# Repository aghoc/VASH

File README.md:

<p align="center">
  <strong>VASH</strong> &nbsp; <em>Vision-Anchored Self-Healing Prosthetic Hand</em><br>
  근전도와 비전 AI를 결합한 사용자 중심 로봇 의수
</p>

<p align="center">
  <a href="#overview">Overview</a> ·
  <a href="#배경과-목표">프로젝트 소개</a> ·
  <a href="#시스템-구성">시스템 구성</a> ·
  <a href="#제작-및-시연">제작 및 시연</a> ·
  <a href="#평가-결과">평가 결과</a> ·
  <a href="#향후-과제">향후 과제</a>
</p>

---

## Overview

다채널 근전도(EMG)와 영상 기반 인공지능을 결합해 사용자의 손동작 의도와 주변 물체를 함께 고려하는 로봇 의수 연구 프로젝트입니다. 근육 피로와 신호 특성 변화에 대응하는 자가치유 제어와 객체 인식 기반 파지 보조를 통해, 일상 환경에 적응하는 사용자 중심의 의수 제어를 목표로 합니다.

> **프로젝트 상태:** 연구 및 개발 단계입니다. Jetson 비전 모듈은 [src/vision/](src/vision/), EMG 판단·의수 제어와 실행 앱은 [src/emg_hand_control/](src/emg_hand_control/), 보드·펌웨어·전극 밴드는 [hardware/](hardware/)에 있습니다. 비전과 EMG 의 실시간 통합은 진행 중입니다. 아래 평가는 각 연구 조건에 한정됩니다.

## 배경과 목표

근전도 기반 의수는 근육에서 발생하는 전기 신호를 이용해 사용자의 동작 의도를 추정합니다. 하지만 근육 피로, 전극 위치, 팔 자세가 바뀌면 신호 특성도 달라져 동작 분류와 제어가 불안정해질 수 있습니다. 또한 EMG만으로는 사용자가 잡으려는 물체의 형태와 크기를 알기 어렵습니다.

VASH는 이 두 문제를 함께 다룹니다.

- **사용자 의도 인식:** 다채널 EMG로 손동작을 분류합니다.
- **신호 변화 대응:** 자가치유(Self-Healing) 제어를 통해 피로와 신호 특성 변화에 따른 성능 저하를 보완하고자 합니다.
- **환경 인식과 파지 보조:** 카메라 영상에서 파지 대상을 찾고 물체에 적합한 그립과 손가락 개구량을 결정하도록 설계합니다.

## 시스템 구성

| 구성 요소 | 역할 |
| --- | --- |
| 16채널 EMG 센서 | 팔의 다채널 근전도 신호 측정 |
| ADS1299 신호 획득 모듈 | EMG 신호 획득 |
| ESP32-S3 | 센서 데이터 처리 및 시스템 제어 |
| 전방 카메라 | 사용자의 시야에 있는 물체 영상 획득 |
| Jetson Orin Nano | EMG·영상 기반 인식과 제어 처리 |
| ORCA Hand | 16자유도 로봇 손을 이용한 파지 동작 |

시스템은 EMG를 통해 **사용자가 어떤 동작을 원하는지** 추정하고, 영상에서 **어떤 물체를 잡으려는지**에 관한 정보를 얻습니다. 두 정보를 바탕으로 로봇 손의 동작을 보조하는 것이 목표입니다.

### EMG 기반 의도 인식과 자가치유

초기에는 팔에 전극을 직접 부착해 근전도 신호를 측정했습니다. 이후 센서 밴드를 직접 설계·제작해 착용하고 손동작 데이터를 수집했습니다.

| 초기 전극 부착 및 근전도 측정 | 직접 설계한 센서 밴드를 이용한 데이터 수집 |
| --- | --- |
|  |  |

EMG 센서에서 얻은 신호로 휴식, 주먹, 세손가락, 집기와 같은 손동작을 구분합니다. 장시간 사용 중 근육 피로가 쌓이거나 측정 조건이 달라지면 같은 동작의 신호도 변할 수 있습니다. VASH의 자가치유 제어는 이러한 신호 변화에 적응해 동작 인식 성능의 저하를 보완하는 것을 목표로 합니다.

| 휴식 | 주먹 |
| --- | --- |
|  |  |
| 세손가락 | 집기 |
|  |  |

*동작별 다채널 EMG 신호 예시. 그림에는 각 동작에 대한 측정 신호가 표시되어 있습니다.*

### Vision AI 기반 파지 보조

전방 카메라 영상에서 객체를 인식하고, 화면 중심과의 거리를 고려하는 **Center Bias** 방식으로 파지 대상을 선정합니다. 선택한 물체의 크기와 형태에 관한 정보를 이용해 적합한 그립과 목표 손가락 개구량을 산출하도록 설계했습니다.

*전방 영상에서 물체를 인식하고 파지 대상을 선정하는 모습.*

*객체 인식 및 대상 선정 화면 예시.*

### 공개된 Jetson 비전 코드

현재 기본 모델은 추가학습하지 않은 공식 **YOLO26m**이며 Jetson에서 생성한 TensorRT FP16 엔진을 사용합니다. ELP IMX291 영상에서 배경 37종을 제외한 물체 43종을 표시하고, 그립을 지원하는 8종에서 중앙 타깃을 선택합니다. 캔·펜 보조 모델은 기본 실행에서 제외했습니다.

- [비전 모듈 설명과 테스트](src/vision/README.md)
- [Jetson 설치·엔진 생성·실행](src/vision/deployment/JETSON_RUNBOOK.md)
- [Jetson → ESP32 UART 규격](src/vision/docs/UART_PROTOCOL.md)

브라우저 뷰어는 그립 제안을 표시하며 UART 송신은 별도 CLI 실행 기능입니다. 가중치·엔진·데이터는 Git에 포함하지 않으며, 모델 복원 스크립트를 제공합니다. 실제 카메라 정확도와 개구량 실측 보정은 추가 검증이 필요합니다.

### 로봇 손과 파지 시뮬레이션

16자유도 ORCA Hand를 사용해 다양한 손가락 동작과 파지를 구현합니다. 시뮬레이션에서는 캔, 펜, 스마트폰, 동전 등 형태가 다른 물체를 대상으로 접근부터 잡기, 들기, 유지까지의 과정을 살펴보았습니다.

*물체와 그립 유형에 따른 파지 동작 시퀀스.*

## 제작 및 시연

| EMG 센서 밴드 착용 시연 | ORCA Hand 구동 테스트 |
| --- | --- |
|  |  |

| 로봇 손 조립 | 손가락 부품 조립 |
| --- | --- |
|  |  |

| 손 부품 3D 프린팅 | 손 부품 3D 프린팅 |
| --- | --- |
|  |  |

## 평가 결과

연구에서는 근육 피로에 따른 동작 분류와 EMG·비전 융합에 따른 파지 선택을 평가했습니다. 아래 그림은 해당 실험 및 분석의 결과를 보여줍니다.

### 피로 상태별 동작 분류

휴식 상태와 피로 측정 시점에 따른 네 가지 동작의 분류 정확도를 비교했습니다. 동작과 측정 시점에 따라 정확도가 달라지는 양상을 확인할 수 있습니다.

### EMG·비전 융합 평가

실측 EMG 기반 오프라인 평가에서 EMG만 사용한 경우와 EMG·비전을 융합한 경우의 파지 선택 오류를 비교했습니다. 그림은 평가한 조건에서 융합 방식의 오류가 더 낮은 결과와, 비전 인식률에 따른 오류 변화를 보여줍니다.

이 결과는 해당 평가 조건에 한정됩니다. 참가자 수, 데이터 수집 및 분할 방법, 자가치유 모델의 구체적인 동작과 실사용 환경에서의 성능은 추가 문서와 검증이 필요합니다. 시뮬레이션 결과를 실제 사용자 대상 성능으로 해석해서는 안 됩니다.

## 저장소 구조

```text
VASH/
├── README.md
├── LICENSE
├── fig/                  # 시스템, EMG 신호 및 평가 결과 이미지
├── docs/                 # 실행·녹화 가이드, 분석 결과
├── hardware/             # ADS1299 보드, ESP32-S3 펌웨어, 전극 밴드
└── src/
    ├── emg_hand_control/ # EMG 판단, ORCA Hand 제어, 실행 앱, Jetson 설치
    └── vision/           # Jetson YOLO26m 검출·타깃 안정화·그립 제안 모듈
```

비전 모듈은 [src/vision/README.md](src/vision/README.md), EMG·의수 제어는 [src/emg_hand_control/README.md](src/emg_hand_control/README.md)를 따릅니다.

## 향후 과제

- 자가치유 제어와 EMG·비전 융합 방식의 구현 및 평가 절차 문서화
- 실제 사용 환경에서의 동작 인식, 파지 성능 및 장시간 안정성 검증
- 전극 위치와 팔 자세 변화 등 다양한 사용 조건에서의 평가
- 하드웨어 경량화와 착용성 개선
- 상지 절단자를 위한 의수 및 재활 보조 기술로의 확장 가능성 검토

## 라이선스

- 코드: [MIT](LICENSE)
- `hardware/demo_glove/`: [CC BY-SA 4.0](hardware/demo_glove/LICENSE.md)
- 그 밖의 하드웨어 파일과 이미지는 위 라이선스에 포함되지 않습니다.

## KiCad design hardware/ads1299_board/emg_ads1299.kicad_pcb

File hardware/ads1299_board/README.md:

# ADS1299 EMG Board

8채널 근전도 측정 보드입니다. ESP32-S3-DevKitC-1 위에 소켓으로 얹어 사용합니다.

위 그림은 KiCad PCB 파일에서 만든 렌더링입니다.

## Specifications

| Item | Value |
|---|---|
| Board | 27 × 96 mm, 2 layers, ENIG |
| AFE | TI ADS1299IPAG (TQFP-64), 8 channels, 24-bit |
| Stream settings | 2000 SPS, gain 24 (±187.5 mV), differential + BIAS |
| Input filter (per channel) | 10 kΩ, 4.7 nF differential, 47 pF common mode |
| Analog supply | 5 V from MAX1683 charge pump + LT1763 LDO |
| Digital supply | 3.3 V from ESP32-S3 |
| Host link | ESP32-S3 UART USB, 921600 baud |

## Block diagram

```mermaid
flowchart LR
    E[Electrodes<br/>8 pairs + BIAS] --> J1[J1]
    J1 --> F[RC input filter]
    F --> U1[ADS1299]
    U1 -- BIAS --> J1
    U1 -- SPI, DRDY --> M[ESP32-S3]
    M -- USB UART --> PC[PC]

    V5[USB 5 V] --> U2[MAX1683<br/>charge pump]
    U2 --> RC[RC filter] --> U3[LT1763<br/>5 V LDO]
    U3 -- AVDD --> U1
    M -- 3V3 DVDD --> U1
```

Analog and digital ground are joined at a single point (NT1).

## Main parts

| Ref | Part | Function |
|---|---|---|
| U1 | ADS1299IPAG | 8-channel analog front end |
| U2 | MAX1683EUK+T | Charge pump |
| U3 | LT1763CS8-5#PBF | 5 V low-noise LDO |
| C1–C8 | 4.7 nF C0G | Differential input filter |
| C9–C24 | 47 pF C0G | Common-mode input filter |
| R18, C25 | 1 MΩ, 1.5 nF | BIAS feedback |
| R24 | 10 Ω | Charge pump RC filter |
| C31 | 100 µF | VCAP1 |
| C47, C48 | 1 µF | Additional AVDD decoupling |
| J1 | 2×9 terminal | Electrode wires |
| J4, J5 | 1×22 socket | ESP32-S3-DevKitC-1 |

Full list with part numbers: [`fabrication/BOM_handsolder.csv`](fabrication/BOM_handsolder.csv)

## J1 electrode terminal

Top view, with the silkscreen labels on the board.

| | | | | | | | | | |
|---|---|---|---|---|---|---|---|---|---|
| Upper row | 1N | 2N | 3N | 4N | BI | 5N | 6N | 7N | 8N |
| Lower row | 1P | 2P | 3P | 4P | GN | 5P | 6P | 7P | 8P |

- `nN`, `nP`: channel n inputs
- `BI`: BIAS electrode
- `GN`: analog ground for scope probes, not an electrode

Clean flux off with IPA after soldering. The ADS1299 inputs are high impedance.

## ESP32-S3 connections

| Board | Signal | ESP32-S3 |
|---|---|---|
| J4.1 | DVDD | 3V3 |
| J4.15 | DRDY | GPIO9 |
| J4.16 | CS | GPIO10 |
| J4.17 | DIN | GPIO11 |
| J4.18 | SCLK | GPIO12 |
| J4.19 | DOUT | GPIO13 |
| J4.20 | START | GPIO14 |
| J4.21 | 5V | 5V |
| J5.17 | RESET | GPIO47 |
| J5.18 | PWDN | GPIO21 |
| J4.22, J5.1, J5.21, J5.22 | GND | GND |

GPIO47 runs at 1.8 V on WROOM-2 modules (`V` suffix), which is too low for RESET. Check the module before use. See [`docs/design_review.md`](docs/design_review.md).

## Test results

Measured on an assembled board with the self-test firmware (2026-11-02).

| Test | Result |
|---|---|
| AVDD / DVDD | 5.008 V / 3.093 V |
| Input-shorted noise, 2000 SPS, gain 24 | 0.394 µVrms (worst channel) |
| Internal test signal | 3.70 mVpp, 2.00 Hz (expected 3.75 mVpp) |

KiCad 10 ERC and DRC report no errors (2026-11-04).

## Files

```
emg_ads1299.kicad_pro    KiCad project
emg_ads1299.kicad_sch    Schematic
emg_ads1299.kicad_pcb    PCB
fp-lib-table             Footprint libraries
sym-lib-table            Symbol libraries
lib/
  symbols/               Project symbols
  footprints/            Project footprints
  3d/                    3D models
fabrication/
  gerber/                Gerber and drill files
  BOM_handsolder.csv     BOM with DigiKey part numbers
  BOM_jlcpcb.csv         BOM for JLCPCB assembly
  CPL_jlcpcb.csv         Placement file for JLCPCB assembly
docs/
  schematic.pdf          Schematic
  design_review.md       Design review
  CHANGELOG.md           Board revision notes
  images/                Board renders
```

Open `emg_ads1299.kicad_pro` in KiCad 10 or later. Library paths are relative to the project folder.

To regenerate the renders:

```bash
kicad-cli pcb render --side top --quality high --width 900 --height 2400 --background transparent -o top.png emg_ads1299.kicad_pcb
kicad-cli sch export pdf -o docs/schematic.pdf emg_ads1299.kicad_sch
```

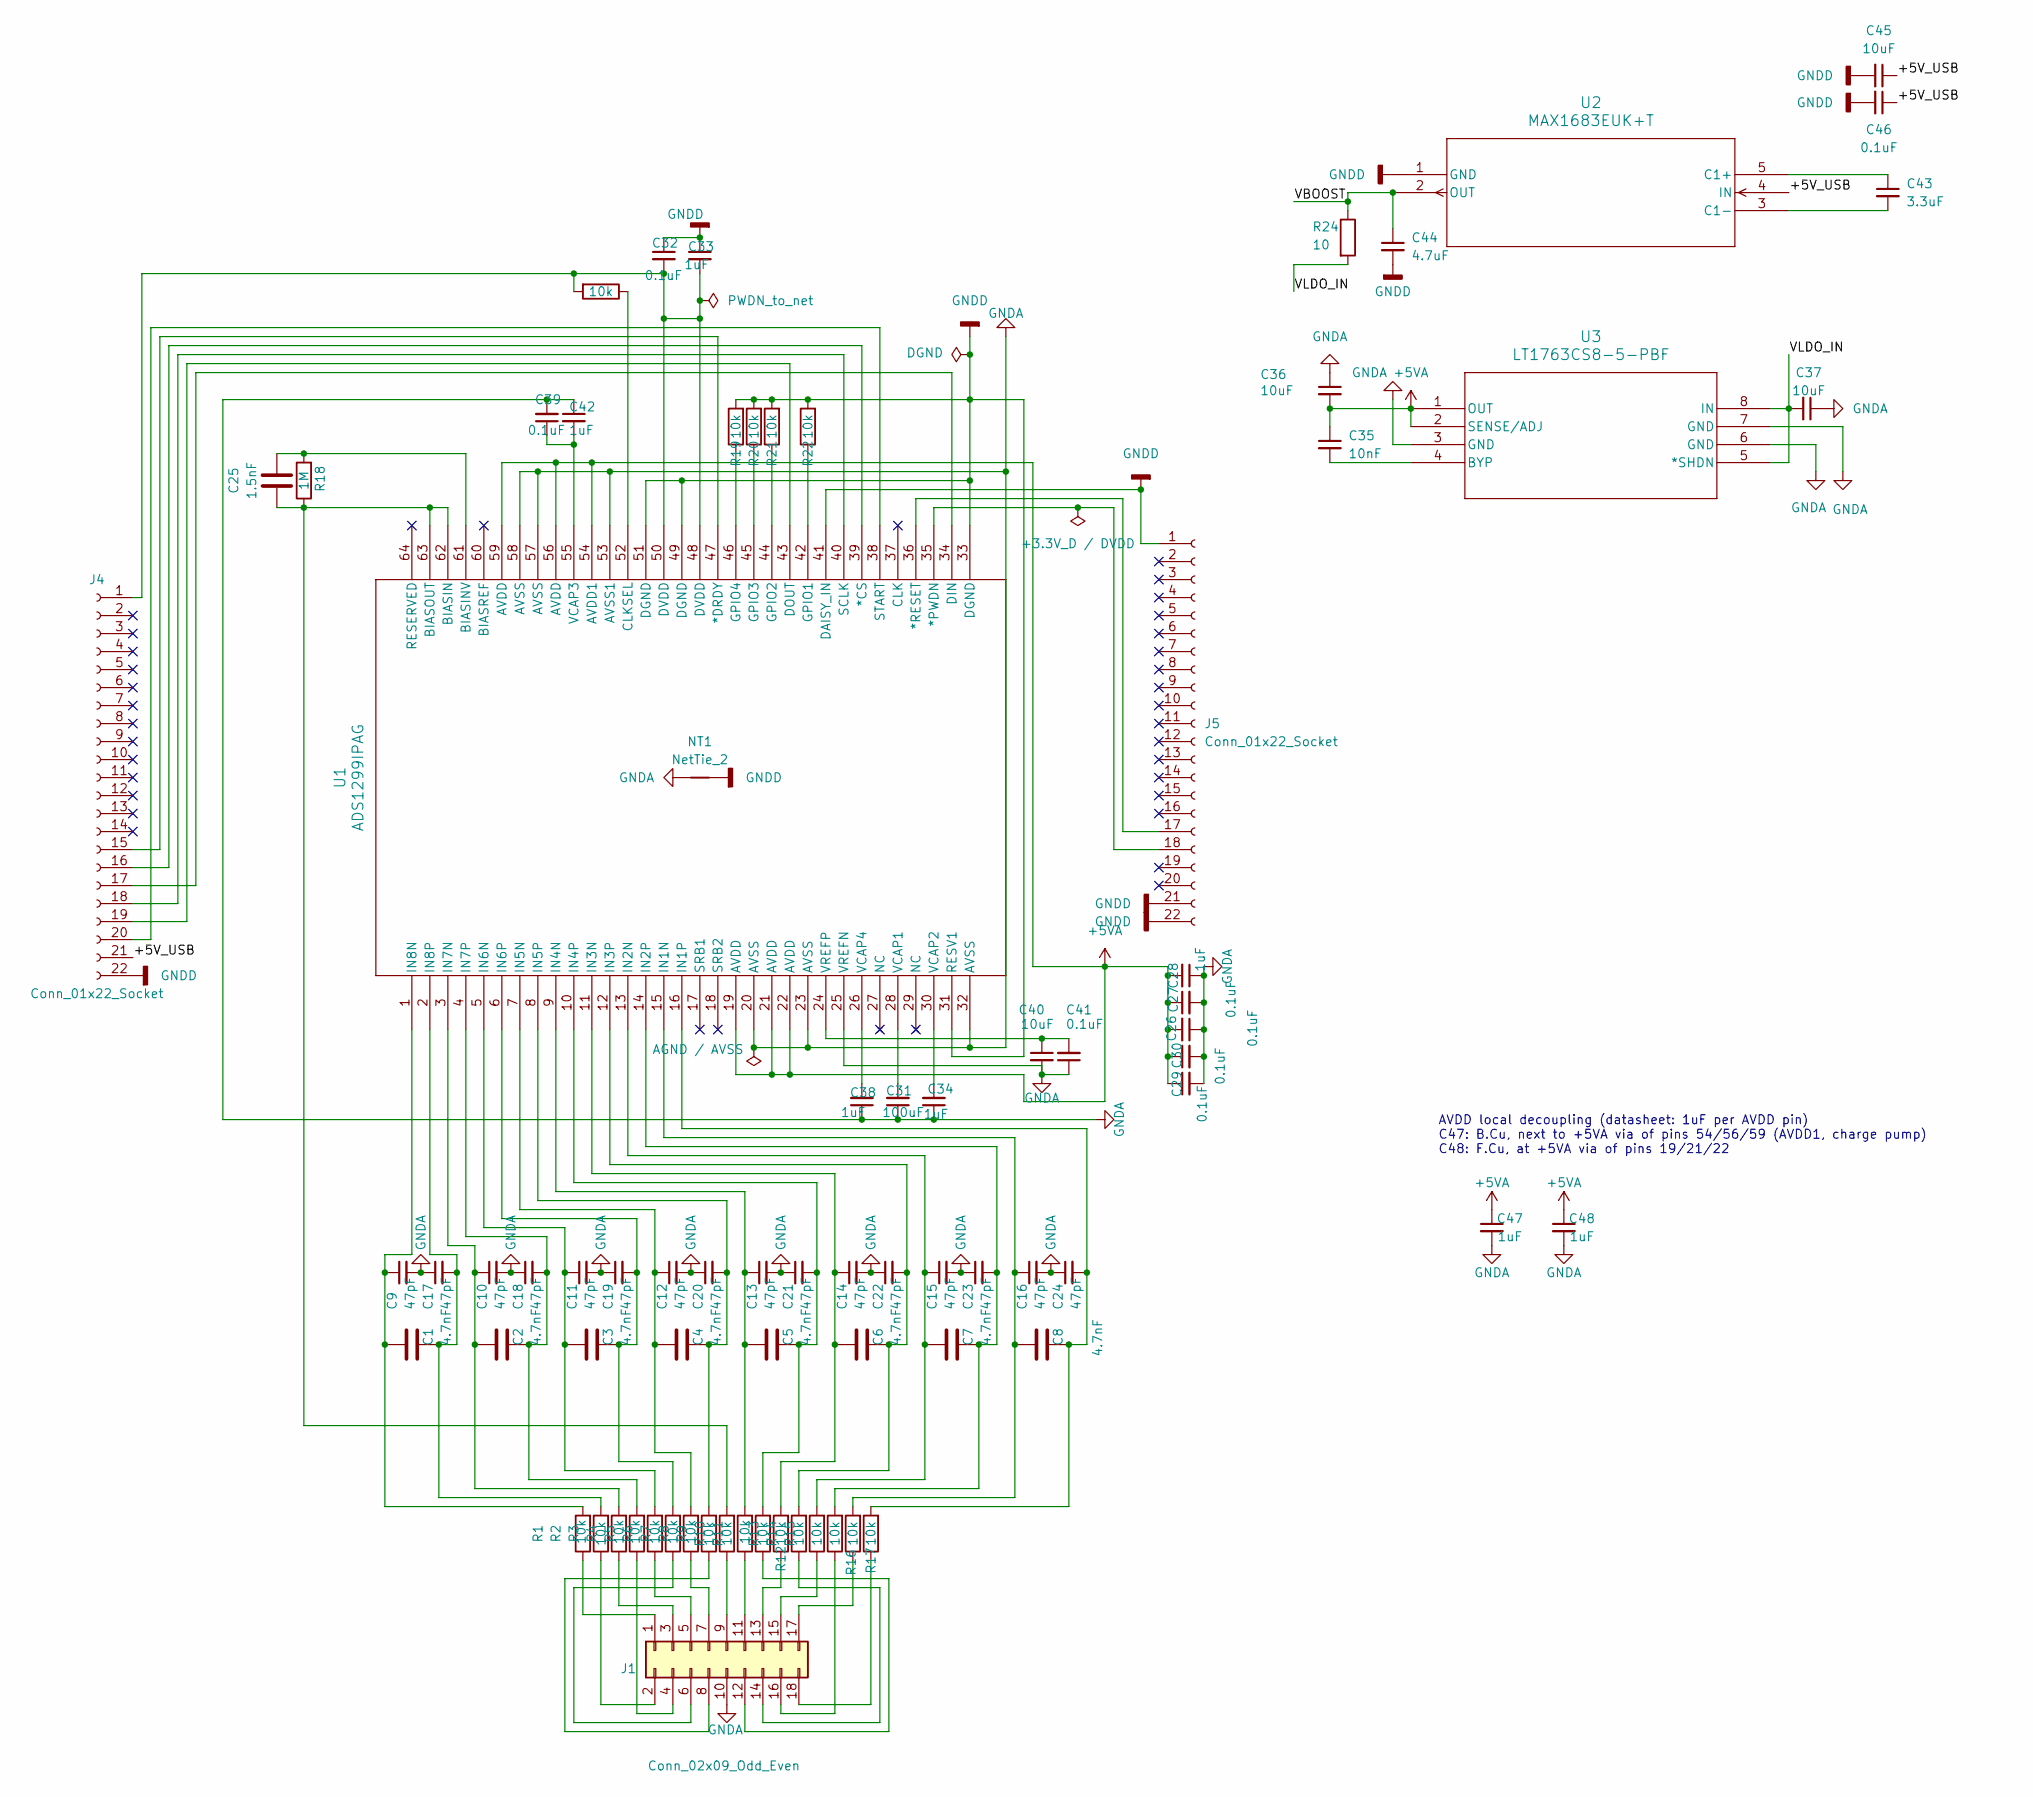
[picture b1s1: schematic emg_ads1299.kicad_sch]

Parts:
C1, C2, C3, C4, C5, C6, C7, C8: 4.7nF; C_1206_3216Metric_Pad1.33x1.80mm_HandSolder
C9, C10, C11, C12, C13, C14, C15, C16, C17, C18, C19, C20, C21, C22, C23, C24: 47pF; C_0805_2012Metric_Pad1.18x1.45mm_HandSolder
C25: 1.5nF; C_0805_2012Metric_Pad1.18x1.45mm_HandSolder
C26, C27, C29, C30, C32, C39, C41, C46: 0.1uF; C_0805_2012Metric_Pad1.18x1.45mm_HandSolder
C28, C33, C34, C38, C42, C47, C48: 1uF; C_0805_2012Metric_Pad1.18x1.45mm_HandSolder
C31: 100uF; C_0805_2012Metric_Pad1.18x1.45mm_HandSolder
C35: 10nF; C_1206_3216Metric_Pad1.33x1.80mm_HandSolder
C36, C37: 10uF; C_1206_3216Metric_Pad1.33x1.80mm_HandSolder
C40, C45: 10uF; C_0805_2012Metric_Pad1.18x1.45mm_HandSolder
C43: 3.3uF; C_0805_2012Metric_Pad1.18x1.45mm_HandSolder
C44: 4.7uF; C_0805_2012Metric_Pad1.18x1.45mm_HandSolder
J1: Conn_02x09_Odd_Even; WireTerminal_2x09_P2.54mm
J4, J5: Conn_01x22_Socket; PinSocket_1x22_P2.54mm_Vertical
NT1: NetTie_2; NetTie-2_SMD_Pad0.5mm
R1, R2, R3, R4, R5, R6, R7, R8, R9, R10, R11, R12, R13, R14, R15, R16, R17, R19, R20, R21, R22, R23: 10k; R_0603_1608Metric_Pad0.98x0.95mm_HandSolder
R18: 1M; R_0603_1608Metric_Pad0.98x0.95mm_HandSolder
R24: 10; R_0805_2012Metric_Pad1.20x1.40mm_HandSolder
U1: ADS1299IPAG; PAG64_TEX
U2: MAX1683EUK+T; SOT-23-5
U3: LT1763CS8-5-PBF; SO-8_S_LIT

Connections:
+5VA: C26.2, C27.1, C28.2, C29.1, C30.1, C35.1, C36.2, C47.1, C48.1, U1.19 (AVDD), U1.21 (AVDD), U1.22 (AVDD), U1.54 (AVDD1), U1.56 (AVDD), U1.59 (AVDD), U3.1 (OUT), U3.2 (SENSE/ADJ)
/+5V_USB: C45.1, C46.1, J4.21, U2.4 (IN)
/VBOOST: C44.1, R24.1, U2.2 (OUT)
/VLDO_IN: C37.2, R24.2, U3.5 (*SHDN), U3.8 (IN)
GNDA: C9.2, C10.2, C11.2, C12.2, C13.2, C14.2, C15.2, C16.2, C17.1, C18.1, C19.1, C20.1, C21.1, C22.1, C23.1, C24.1, C26.1, C27.2, C28.1, C29.2, C30.2, C31.1, C34.1, C36.1, C37.1, C38.1, C39.2, C40.2, C41.1, C42.1, C47.2, C48.2, J1.10, NT1.1, U1.20 (AVSS), U1.23 (AVSS), U1.25 (VREFN), U1.32 (AVSS), U1.53 (AVSS1), U1.57 (AVSS), U1.58 (AVSS), U3.3 (GND), U3.6 (GND), U3.7 (GND)
GNDD: C32.1, C33.1, C44.2, C45.2, C46.2, J4.22, J5.1, J5.21, J5.22, NT1.2, R19.2, R20.2, R21.2, R22.2, U1.31 (RESV1), U1.33 (DGND), U1.41 (DAISY_IN), U1.49 (DGND), U1.51 (DGND), U2.1 (GND)
unnamed: J1.1, R1.1
unnamed: J1.2, R2.1
unnamed: J1.3, R3.1
unnamed: J1.4, R4.1
unnamed: J1.5, R5.1
unnamed: J1.6, R6.1
unnamed: J1.7, R7.1
unnamed: J1.8, R8.1
unnamed: J1.9, R9.1
unnamed: J1.11, R10.1
unnamed: J1.12, R11.1
unnamed: J1.13, R12.1
unnamed: J1.14, R13.1
unnamed: J1.15, R14.1
unnamed: J1.16, R15.1
unnamed: J1.17, R16.1
unnamed: J1.18, R17.1
unnamed: C32.2, C33.2, J4.1, R23.2, U1.48 (DVDD), U1.50 (DVDD)
unnamed: J4.15, U1.47 (*DRDY)
unnamed: J4.16, U1.39 (*CS)
unnamed: J4.17, U1.34 (DIN)
unnamed: J4.18, U1.40 (SCLK)
unnamed: J4.19, U1.43 (DOUT)
unnamed: J4.20, U1.38 (START)
unnamed: J5.17, U1.36 (*RESET)
unnamed: J5.18, U1.35 (*PWDN)
unnamed: C25.1, R9.2, R18.1, U1.62 (BIASIN), U1.63 (BIASOUT)
unnamed: C25.2, R18.2, U1.61 (BIASINV)
unnamed: R23.1, U1.52 (CLKSEL)
unnamed: R22.1, U1.42 (GPIO1)
unnamed: R21.1, U1.44 (GPIO2)
unnamed: R20.1, U1.45 (GPIO3)
unnamed: R19.1, U1.46 (GPIO4)
unnamed: C8.1, C16.1, R16.2, U1.15 (IN1N)
unnamed: C8.2, C24.2, R17.2, U1.16 (IN1P)
unnamed: C7.1, C15.1, R14.2, U1.13 (IN2N)
unnamed: C7.2, C23.2, R15.2, U1.14 (IN2P)
unnamed: C6.1, C14.1, R12.2, U1.11 (IN3N)
unnamed: C6.2, C22.2, R13.2, U1.12 (IN3P)
unnamed: C5.1, C13.1, R10.2, U1.9 (IN4N)
unnamed: C5.2, C21.2, R11.2, U1.10 (IN4P)
unnamed: C4.1, C12.1, R7.2, U1.7 (IN5N)
unnamed: C4.2, C20.2, R8.2, U1.8 (IN5P)
unnamed: C3.1, C11.1, R5.2, U1.5 (IN6N)
unnamed: C3.2, C19.2, R6.2, U1.6 (IN6P)
unnamed: C2.1, C10.1, R3.2, U1.3 (IN7N)
unnamed: C2.2, C18.2, R4.2, U1.4 (IN7P)
unnamed: C1.1, C9.1, R1.2, U1.1 (IN8N)
unnamed: C1.2, C17.2, R2.2, U1.2 (IN8P)
unnamed: C31.2, U1.28 (VCAP1)
unnamed: C34.2, U1.30 (VCAP2)
unnamed: C39.1, C42.2, U1.55 (VCAP3)
unnamed: C38.2, U1.26 (VCAP4)
unnamed: C40.1, C41.2, U1.24 (VREFP)
unnamed: C43.1, U2.5 (C1+)
unnamed: C43.2, U2.3 (C1-)
unnamed: C35.2, U3.4 (BYP)

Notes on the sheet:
AVDD local decoupling (datasheet: 1uF per AVDD pin) C47: B.Cu, next to +5VA via of pins 54/56/59 (AVDD1, charge pump) C48: F.Cu, at +5VA via of pins 19/21/22

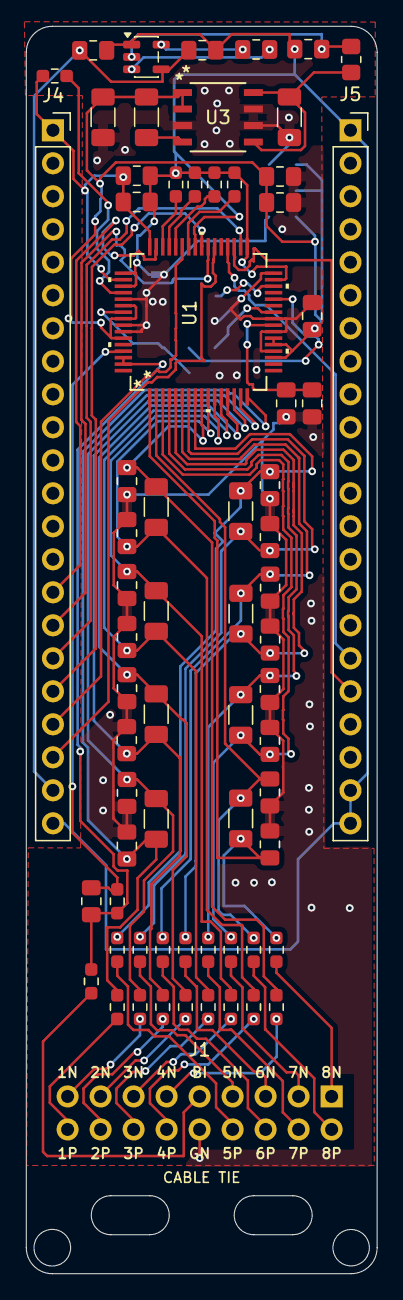
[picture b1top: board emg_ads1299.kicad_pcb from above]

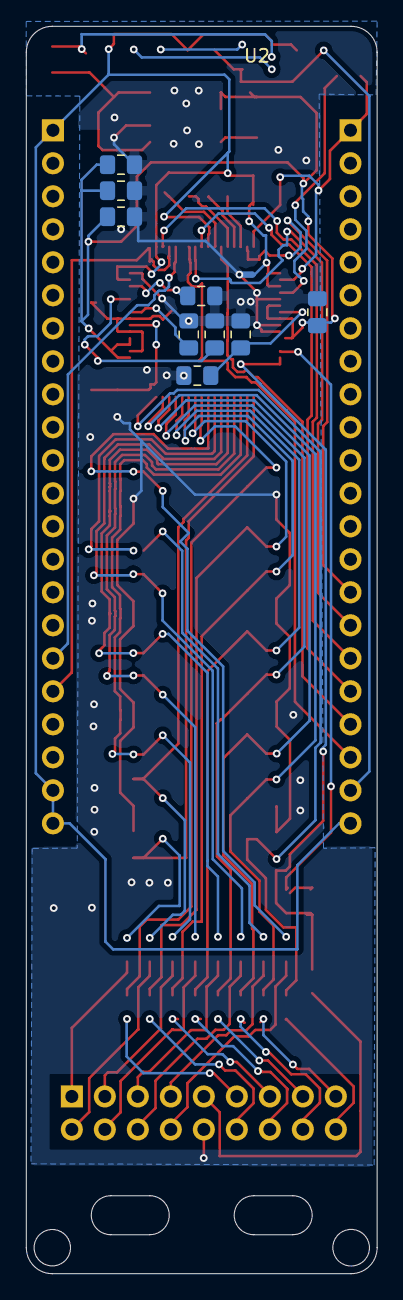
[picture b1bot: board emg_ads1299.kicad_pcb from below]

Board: 2 copper layers, 27.0 x 96.0 mm, 79 parts (10 on the bottom side), 63 nets.

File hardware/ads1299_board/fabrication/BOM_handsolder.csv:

Designator,Qty/board,Value,Package,DigiKey PN,Manufacturer PN,Note
"C9-C24",16,47pF 50V C0G,0805,399-C0805C470J5GACTUCT-ND,C0805C470J5GACTU,input CM filter
C25,1,1.5nF 100V C0G,0805,490-11552-1-ND,GRM2165C2A152JA01D,BIAS feedback
"C1-C8",8,4.7nF 50V C0G,1206,478-KGM31TCG1H472JUCT-ND,KGM31TCG1H472JU,input diff filter
C35,1,10nF 50V X7R,1206,399-C1206C103K5RACTUCT-ND,C1206C103K5RACTU,LDO BYP
"C26,C27,C29,C30,C32,C39,C41,C46",8,0.1uF 25V X7R,0805,478-KGM21NR71E104KTCT-ND,KGM21NR71E104KT,
"C28,C33,C34,C38,C42,C47,C48",7,1uF 25V X7R,0805,399-C0805C105K3RACTUCT-ND,C0805C105K3RACTU,C47/C48 = AVDD local decoupling (added 09-26)
C43,1,3.3uF 25V X5R,0805,732-7627-1-ND,885012107017,charge pump flying cap
C44,1,4.7uF 25V X7R,0805,587-2990-1-ND,TMK212AB7475KG-T,changed from 10uF (09-26)
"C36,C37",2,10uF 25V X5R,1206,1276-1075-1-ND,CL31A106KAHNNNE,LDO out / in
"C40,C45",2,10uF 16V X7R,0805,1276-2872-1-ND,CL21B106KOQNNNE,VREFP / charge pump in
C31,1,100uF 6.3V X5R,0805,1276-CL21A107MQYNNWECT-ND,CL21A107MQYNNWE,VCAP1
"R1-R17,R19-R23",22,10k 1%,0603,541-10.0KHCT-ND,CRCW060310K0FKEA,
R18,1,1M 1%,0603,541-1.00MHCT-ND,CRCW06031M00FKEA,BIAS feedback
R24,1,10R 1%,0805,541-10.0CCT-ND,CRCW080510R0FKEA,charge pump RC filter
U2,1,MAX1683EUK+T,SOT-23-5,MAX1683EUK+TCT-ND,MAX1683EUK+T,
U3,1,LT1763CS8-5#PBF,SO-8,505-LT1763CS8-5#PBF-ND,LT1763CS8-5#PBF,
"J4,J5",2,22-pin female socket,TH 2.54,S7055-ND,PPPC221LFBN-RC,ESP32-S3-DevKitC-1
U1,1,ADS1299IPAG,TQFP-64,-,-,already owned
J1,1,wire terminal 2x9,TH 2.54,-,-,electrode wires soldered directly
NT1,0,NetTie,-,-,-,copper only
